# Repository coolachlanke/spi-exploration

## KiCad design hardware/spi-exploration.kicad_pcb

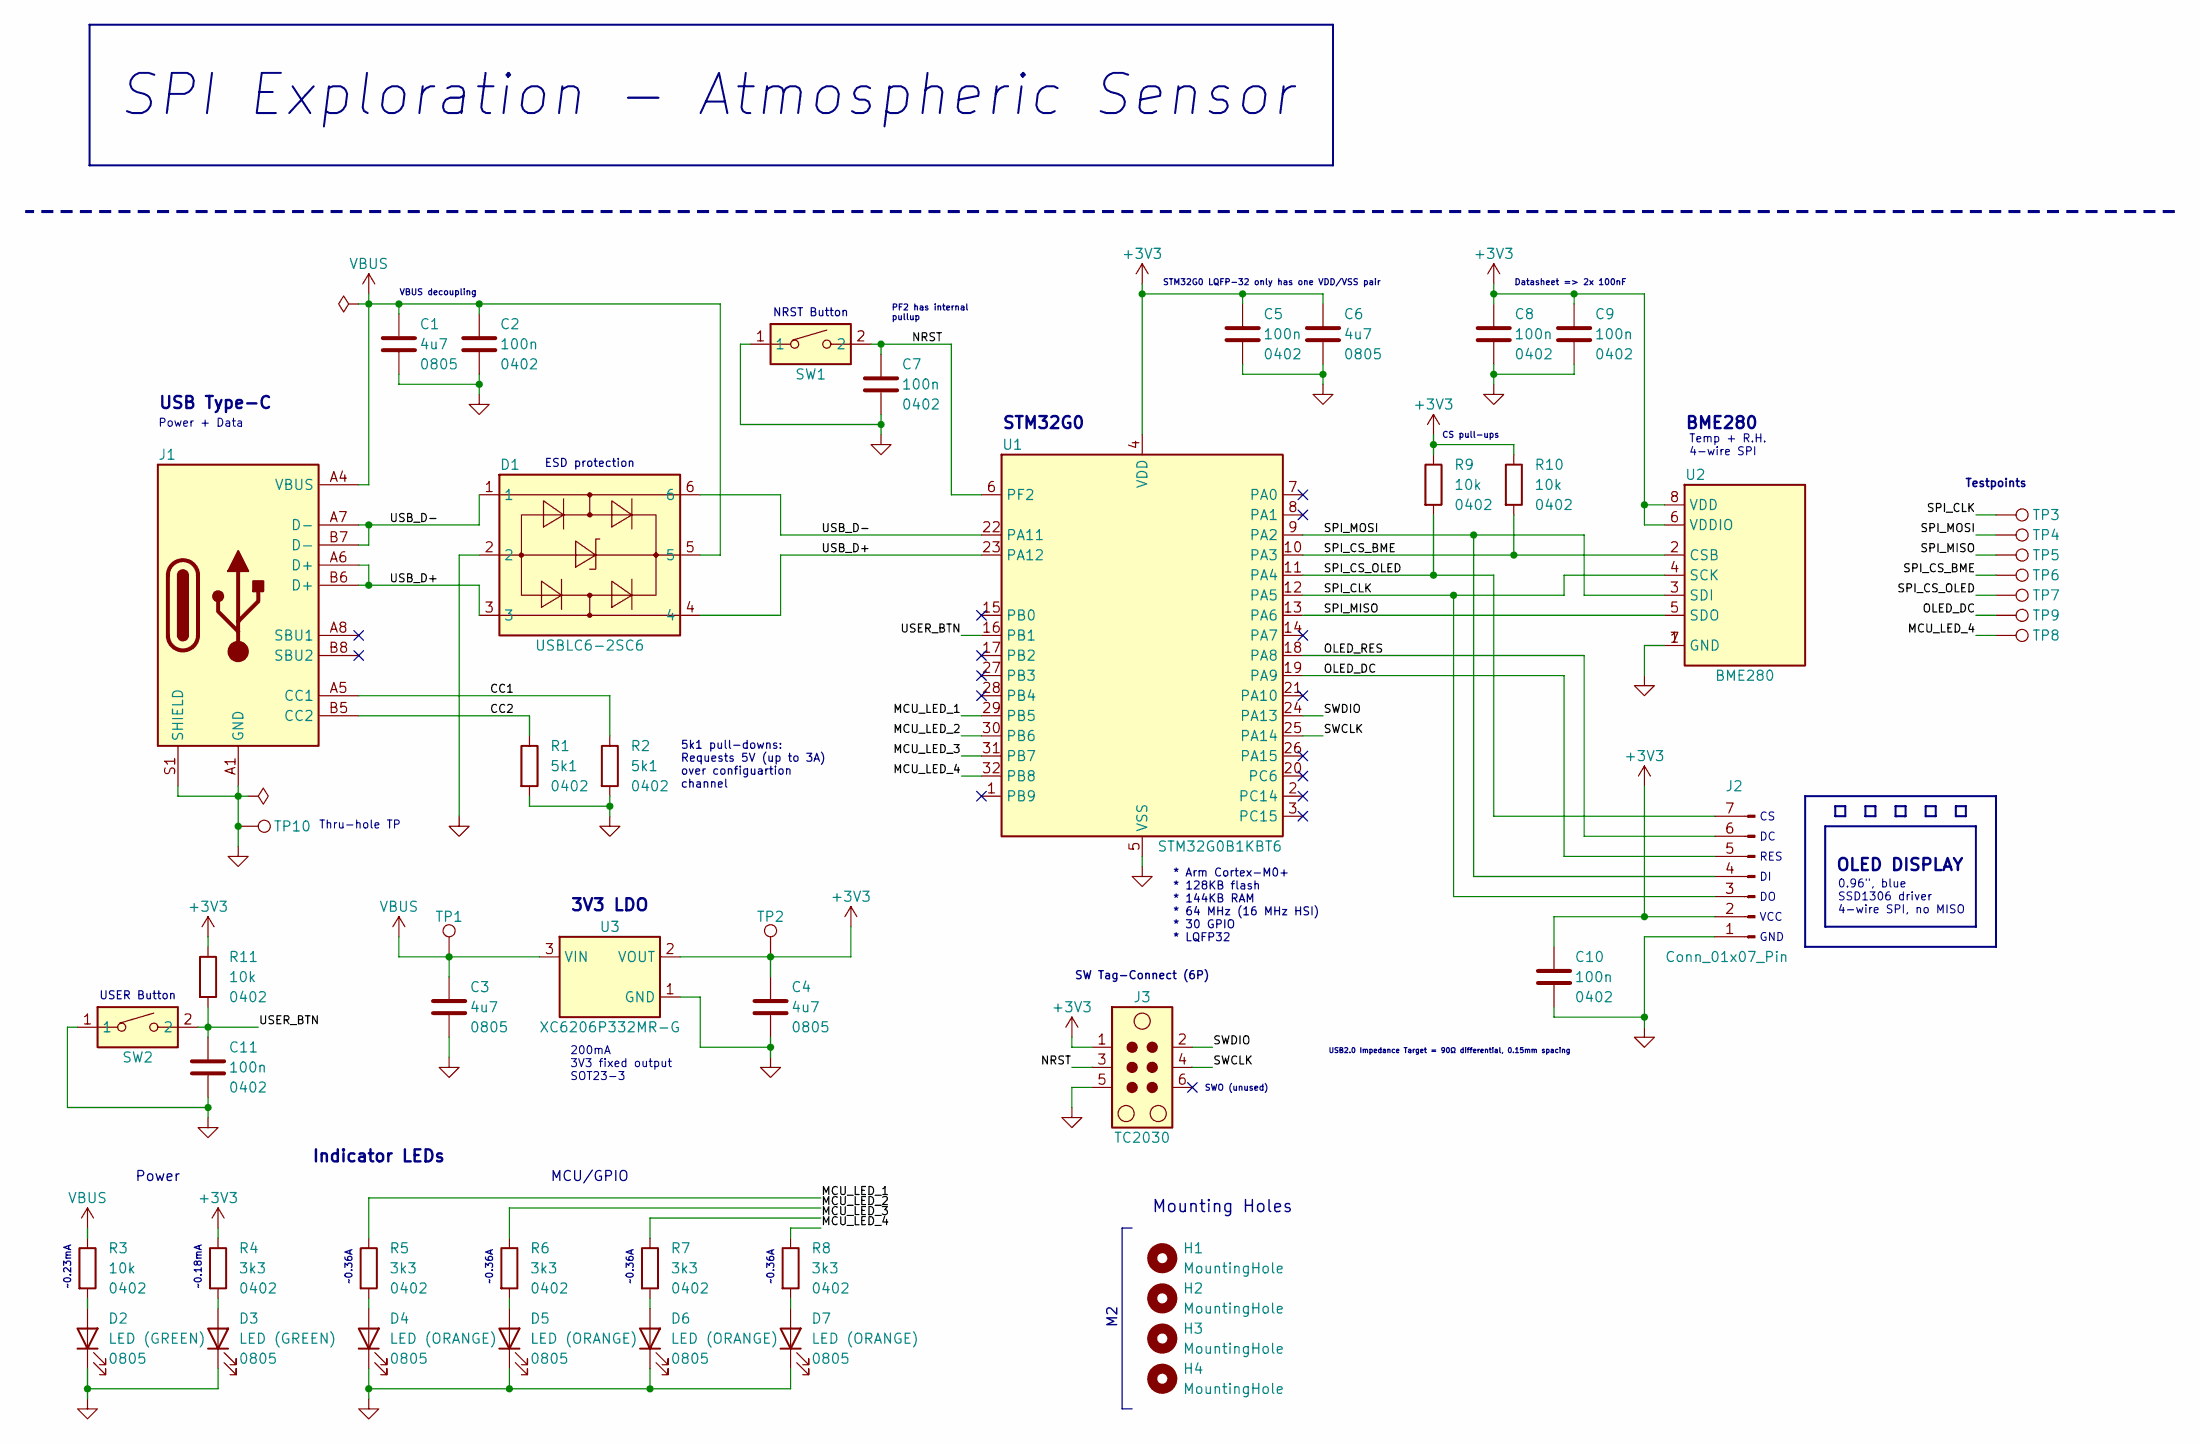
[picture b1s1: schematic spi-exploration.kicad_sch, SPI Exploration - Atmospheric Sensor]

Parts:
C1, C3, C4, C6: 4u7; C_0805_2012Metric; LCSC C1779
C2, C5, C7, C8, C9, C10, C11: 100n; C_0402_1005Metric; LCSC C1525
D1: USBLC6-2SC6; SOT-23-6_L2.9-W1.6-P0.95-LS2.8-BL; LCSC Part C7519
D2, D3: LED (GREEN); LED_0805_2012Metric; LCSC C2297
D4, D5, D6, D7: LED (ORANGE); LED_0805_2012Metric; LCSC C2296
H1, H2, H3, H4: MountingHole; MountingHole_2.2mm_M2
J1: USB_C_Receptacle_USB2.0_16P; NEW_USB-C-SMD_TYPE-C-6PIN-2MD-073; LCSC Part C2765186
J2: Conn_01x07_Pin; PinHeader_1x07_P2.54mm_Vertical
J3: TC2030; Tag-Connect_TC2030-IDC-NL_2x03_P1.27mm_Vertical
R1, R2: 5k1; R_0402_1005Metric; LCSC C25905
R3, R9, R10, R11: 10k; R_0402_1005Metric; LCSC C25744
R4, R5, R6, R7, R8: 3k3; R_0402_1005Metric; LCSC C25890
SW1, SW2: TS-1088-AR02016; SW-SMD_L3.9-W3.0-P4.45; MPN TS-1088-AR02016; LCSC Part C720477
TP1, TP2, TP3, TP4, TP5, TP6, TP7, TP8, TP9: TestPoint; TestPoint_Pad_D1.0mm
TP10: TestPoint; TestPoint_THTPad_D2.0mm_Drill1.0mm
U1: STM32G0B1KBT6; LQFP-32_7x7mm_P0.8mm; LCSC C7021416
U2: BME280; LGA-8_BME280_BL; MPN BME280; LCSC Part C92489
U3: XC6206P332MR-G; SOT-23-3_L2.9-W1.6-P1.90-LS2.8-BR; LCSC Part C5446

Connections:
+3V3: C4.1, C5.1, C6.1, C8.1, C9.1, C10.1, J2.2, J3.1, R4.1, R9.1, R10.1, R11.1, TP2.1 (1_1), U1.4 (VDD), U2.6 (VDDIO), U2.8 (VDD), U3.2 (VOUT)
/CC1: J1.A5 (CC1), R2.1
/CC2: J1.B5 (CC2), R1.1
/MCU_LED_1: R5.1, U1.29 (PB5)
/MCU_LED_2: R6.1, U1.30 (PB6)
/MCU_LED_3: R7.1, U1.31 (PB7)
/MCU_LED_4: R8.1, TP8.1 (1_1), U1.32 (PB8)
/NRST: C7.1, J3.3, SW1.2, U1.6 (PF2)
/OLED_DC: J2.5, TP9.1 (1_1), U1.19 (PA9)
/OLED_RES: J2.6, U1.18 (PA8)
/SPI_CLK: J2.3, TP3.1 (1_1), U1.12 (PA5), U2.4 (SCK)
/SPI_CS_BME: R10.2, TP6.1 (1_1), U1.10 (PA3), U2.2 (CSB)
/SPI_CS_OLED: J2.7, R9.2, TP7.1 (1_1), U1.11 (PA4)
/SPI_MISO: TP5.1 (1_1), U1.13 (PA6), U2.5 (SDO)
/SPI_MOSI: J2.4, TP4.1 (1_1), U1.9 (PA2), U2.3 (SDI)
/SWCLK: J3.4, U1.25 (PA14)
/SWDIO: J3.2, U1.24 (PA13)
/USB_D+: D1.3, D1.4, J1.A6 (D+), J1.B6 (D+), U1.23 (PA12)
/USB_D-: D1.1, D1.6, J1.A7 (D-), J1.B7 (D-), U1.22 (PA11)
/USER_BTN: C11.1, R11.2, SW2.2, U1.16 (PB1)
GND: C1.2, C2.2, C3.2, C4.2, C5.2, C6.2, C7.2, C8.2, C9.2, C10.2, C11.2, D1.2, D2.1 (K), D3.1 (K), D4.1 (K), D5.1 (K), D6.1 (K), D7.1 (K), J1.A1 (GND), J1.A12 (GND), J1.B1 (GND), J1.B12 (GND), J1.S1 (SHIELD), J2.1, J3.5, R1.2, R2.2, SW1.1, SW2.1, TP10.1 (1_1), U1.5 (VSS), U2.1 (GND), U2.7 (GND), U3.1 (GND)
unnamed: D2.2 (A), R3.2
unnamed: D3.2 (A), R4.2
unnamed: D4.2 (A), R5.2
unnamed: D5.2 (A), R6.2
unnamed: D6.2 (A), R7.2
unnamed: D7.2 (A), R8.2
VBUS: C1.1, C2.1, C3.1, D1.5, J1.A4 (VBUS), J1.A9 (VBUS), J1.B4 (VBUS), J1.B9 (VBUS), R3.1, TP1.1 (1_1), U3.3 (VIN)

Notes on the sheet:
0.96", blue SSD1306 driver 4-wire SPI, no MISO
Temp + R.H. 4-wire SPI
Indicator LEDs
~0.36A
SW Tag-Connect (6P)
5k1 pull-downs: Requests 5V (up to 3A) over configuartion channel
USER Button
OLED DISPLAY
BME280
STM32G0
~0.18mA
CS pull-ups
3V3 LDO
Thru-hole TP
VCC
* Arm Cortex-M0+ * 128KB flash * 144KB RAM * 64 MHz (16 MHz HSI) * 30 GPIO * LQFP32
USB2.0 Impedance Target = 90Ω differential, 0.15mm spacing
MCU/GPIO
Datasheet => 2x 100nF
PF2 has internal pullup
200mA 3V3 fixed output SOT23-3
NRST Button
RES
USB Type-C
STM32G0 LQFP-32 only has one VDD/VSS pair
GND
~0.23mA
Mounting Holes
Power + Data
ESD protection
VBUS decoupling
SWO (unused)
SPI Exploration - Atmospheric Sensor
Power
Testpoints

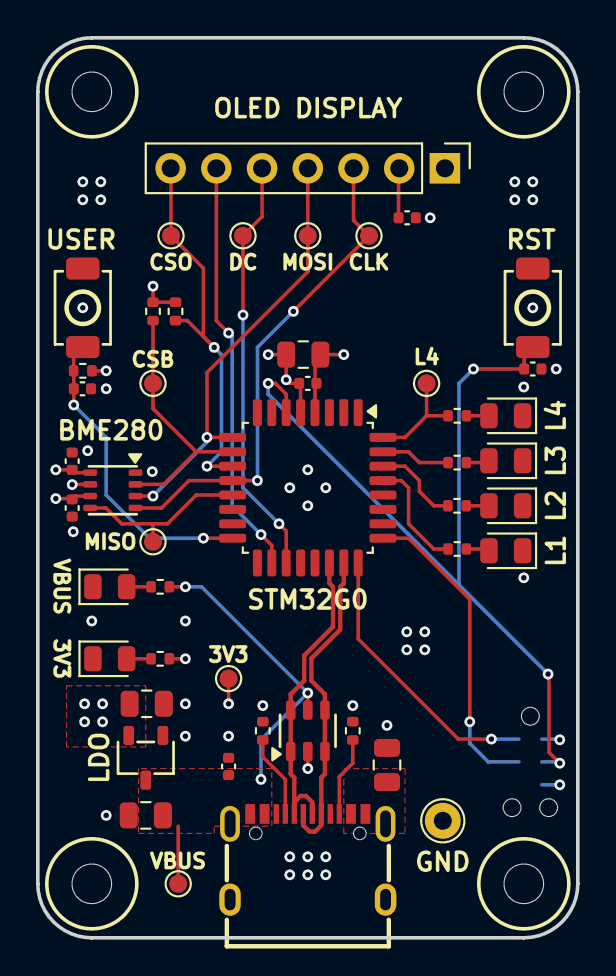
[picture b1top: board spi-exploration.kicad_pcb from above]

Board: 4 copper layers, 30.0 x 50.0 mm, 51 parts (1 on the bottom side), 28 nets.

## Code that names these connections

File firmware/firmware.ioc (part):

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Mcu.Name=STM32G0B1K(B-C-E)Tx
Mcu.Package=LQFP32
Mcu.UserName=STM32G0B1KBTx
PA0.Mode=Asynchronous
PA0.Signal=USART4_TX
PA1.Mode=Asynchronous
PA1.Signal=USART4_RX
PA13.Mode=Serial_Wire
PA13.Signal=SYS_SWDIO
PA14-BOOT0.Mode=Serial_Wire
PA14-BOOT0.Signal=SYS_SWCLK
PA2.GPIOParameters=GPIO_Label
PA2.GPIO_Label=OLED_SPI_MOSI
PA2.Mode=Full_Duplex_Master
PA2.Signal=SPI1_MOSI
PA5.GPIOParameters=GPIO_Label
PA5.GPIO_Label=OLED_SPI_CLK
PA5.Mode=Full_Duplex_Master
PA5.Signal=SPI1_SCK
PA6.GPIOParameters=GPIO_Label
PA6.GPIO_Label=OLED_SPI_MISO
PA6.Mode=Full_Duplex_Master
PA6.Signal=SPI1_MISO
RCC.HSE_VALUE=8000000
RCC.SYSCLKFreq_VALUE=64000000
RCC.SYSCLKSource=RCC_SYSCLKSOURCE_PLLCLK
board=custom
